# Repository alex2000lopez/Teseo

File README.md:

# Teseo
PCB for Teseo, a maze runner robot designed for MakersUPV

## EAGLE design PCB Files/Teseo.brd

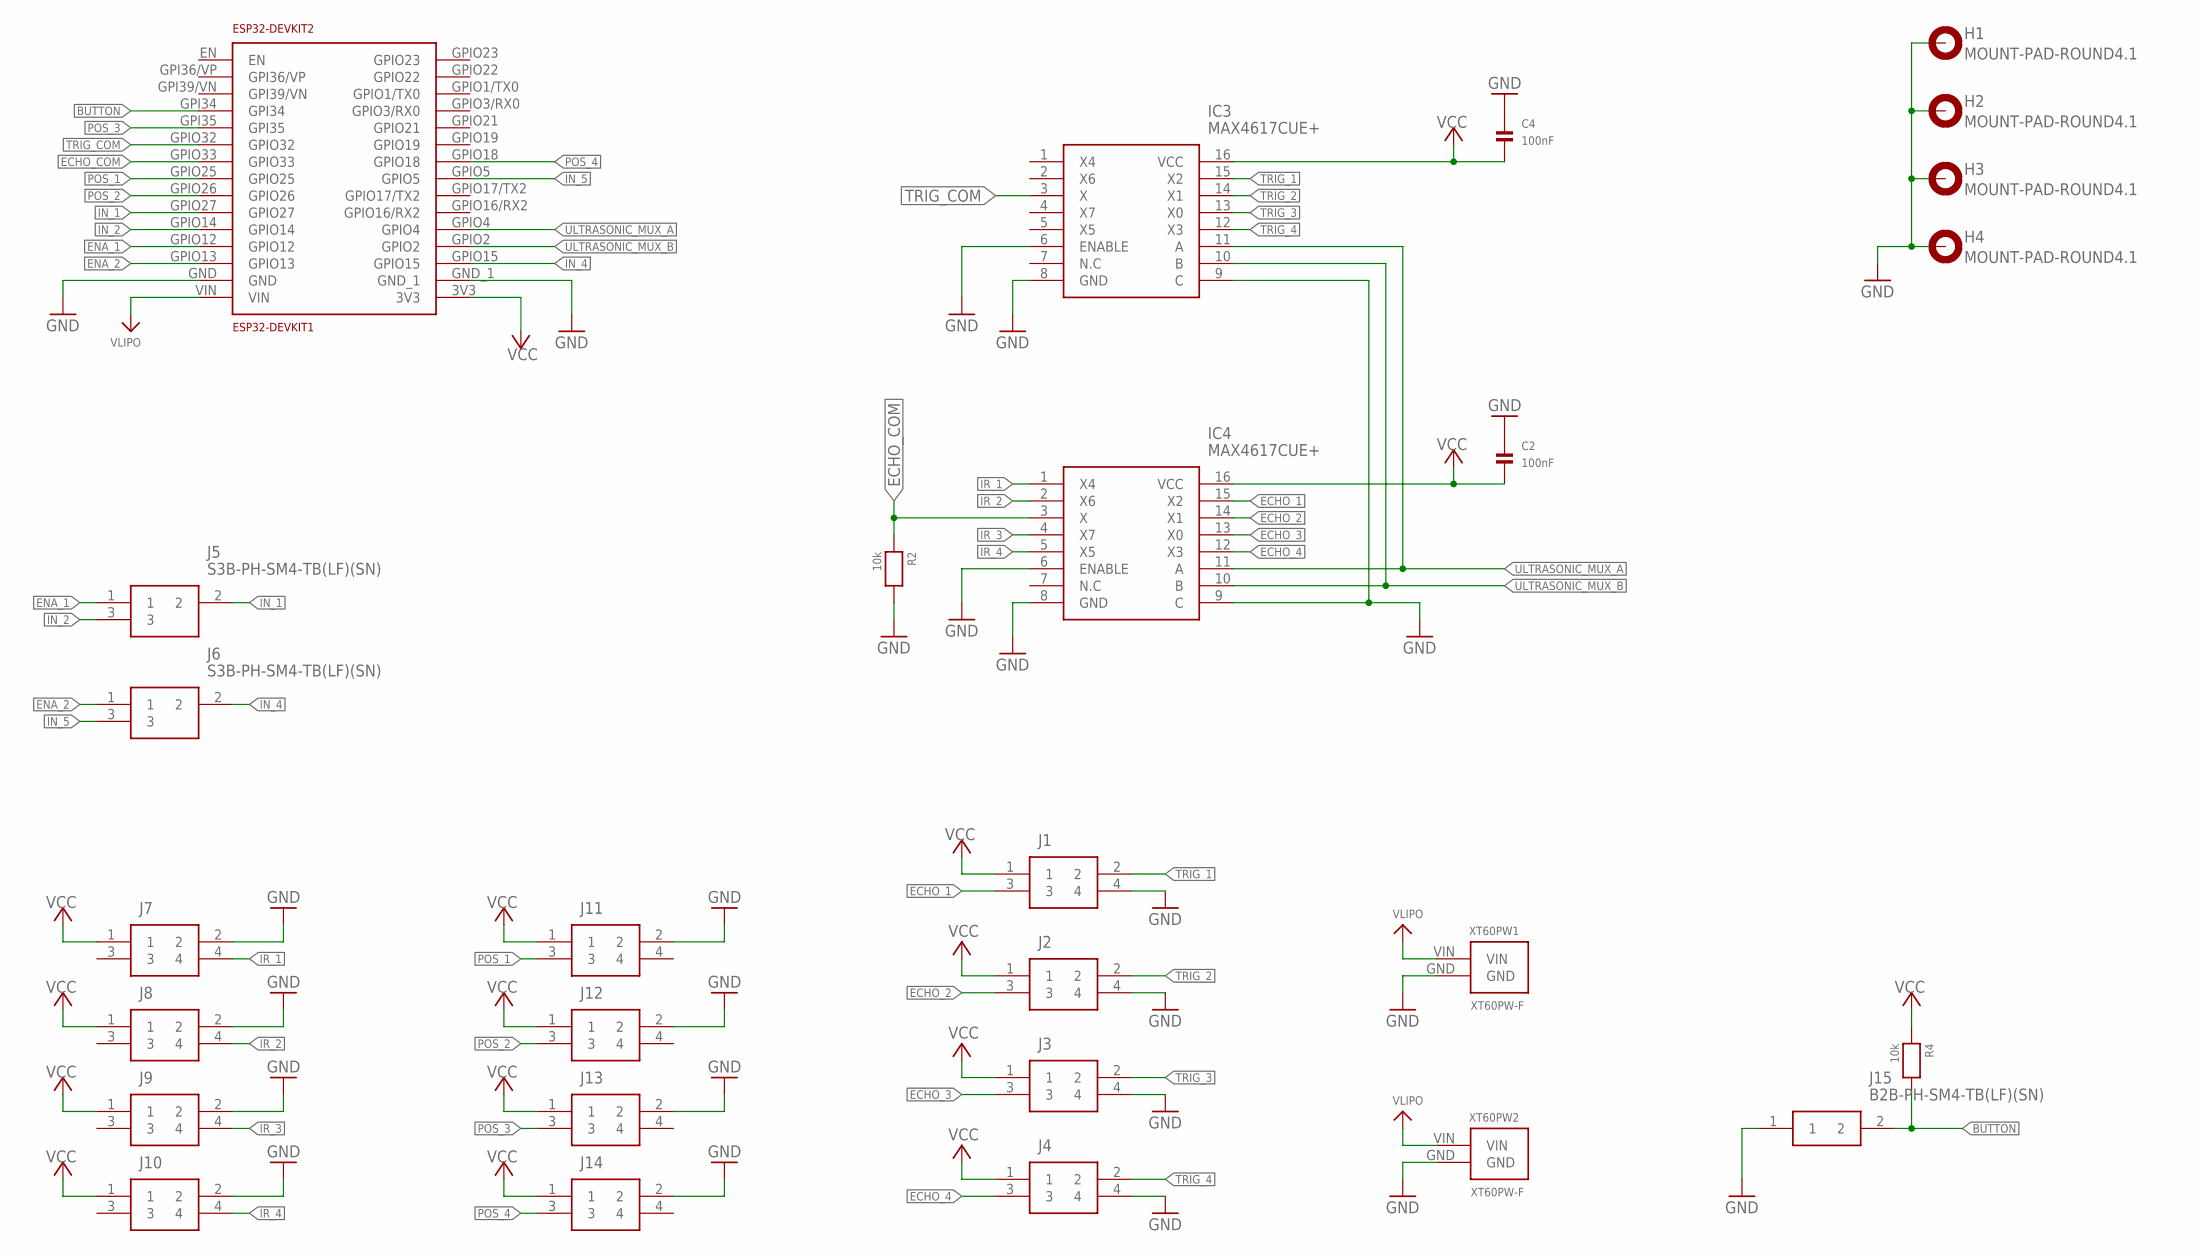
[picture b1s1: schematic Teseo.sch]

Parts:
C2, C4: 100nF; 0805
ESP32-DEVKIT2: ESP32-DEVKIT1
H1, H2, H3, H4: MOUNT-PAD-ROUND4.1; 4,1-PAD
IC3, IC4: MAX4617CUE+; SOP65P640X110-16N
J1, J2, J3, J4, J7, J8, J9, J10, J11, J12, J13, J14: S4B-PH-SM4-TB(LF)(SN); S4B-PH-SM4-TB
J5, J6: S3B-PH-SM4-TB(LF)(SN); S3B-PH-SM4-TB
J15: B2B-PH-SM4-TB(LF)(SN); B2B-PH-SM4-TB
R2, R4: 10k; _0805
XT60PW1, XT60PW2: XT60PW-F

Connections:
BUTTON: ESP32-DEVKIT2.GPI34, J15.2, R4.2
ECHO_1: IC4.15 (X2), J1.3
ECHO_2: IC4.14 (X1), J2.3
ECHO_3: IC4.13 (X0), J3.3
ECHO_4: IC4.12 (X3), J4.3
ECHO_COM: ESP32-DEVKIT2.GPIO33, IC4.3 (X), R2.1
ENA_1: ESP32-DEVKIT2.GPIO12, J5.1
ENA_2: ESP32-DEVKIT2.GPIO13, J6.1
GND: C2.1, C4.1, ESP32-DEVKIT2.GND, ESP32-DEVKIT2.GND_1, H1.B4,1, H2.B4,1, H3.B4,1, H4.B4,1, IC3.6 (ENABLE), IC3.8 (GND), IC3.9 (C), IC4.6 (ENABLE), IC4.8 (GND), IC4.9 (C), J1.4, J2.4, J3.4, J4.4, J7.2, J8.2, J9.2, J10.2, J11.2, J12.2, J13.2, J14.2, J15.1, R2.2, XT60PW1.GND, XT60PW2.GND
IN_1: ESP32-DEVKIT2.GPIO27, J5.2
IN_2: ESP32-DEVKIT2.GPIO14, J5.3
IN_4: ESP32-DEVKIT2.GPIO15, J6.2
IN_5: ESP32-DEVKIT2.GPIO5, J6.3
IR_1: IC4.1 (X4), J7.4
IR_2: IC4.2 (X6), J8.4
IR_3: IC4.4 (X7), J9.4
IR_4: IC4.5 (X5), J10.4
POS_1: ESP32-DEVKIT2.GPIO25, J11.3
POS_2: ESP32-DEVKIT2.GPIO26, J12.3
POS_3: ESP32-DEVKIT2.GPI35, J13.3
POS_4: ESP32-DEVKIT2.GPIO18, J14.3
TRIG_1: IC3.15 (X2), J1.2
TRIG_2: IC3.14 (X1), J2.2
TRIG_3: IC3.13 (X0), J3.2
TRIG_4: IC3.12 (X3), J4.2
TRIG_COM: ESP32-DEVKIT2.GPIO32, IC3.3 (X)
ULTRASONIC_MUX_A: ESP32-DEVKIT2.GPIO4, IC3.11 (A), IC4.11 (A)
ULTRASONIC_MUX_B: ESP32-DEVKIT2.GPIO2, IC3.10 (B), IC4.10 (B)
VCC: C2.2, C4.2, ESP32-DEVKIT2.3V3, IC3.16 (VCC), IC4.16 (VCC), J1.1, J2.1, J3.1, J4.1, J7.1, J8.1, J9.1, J10.1, J11.1, J12.1, J13.1, J14.1, R4.1
VLIPO: ESP32-DEVKIT2.VIN, XT60PW1.VIN, XT60PW2.VIN

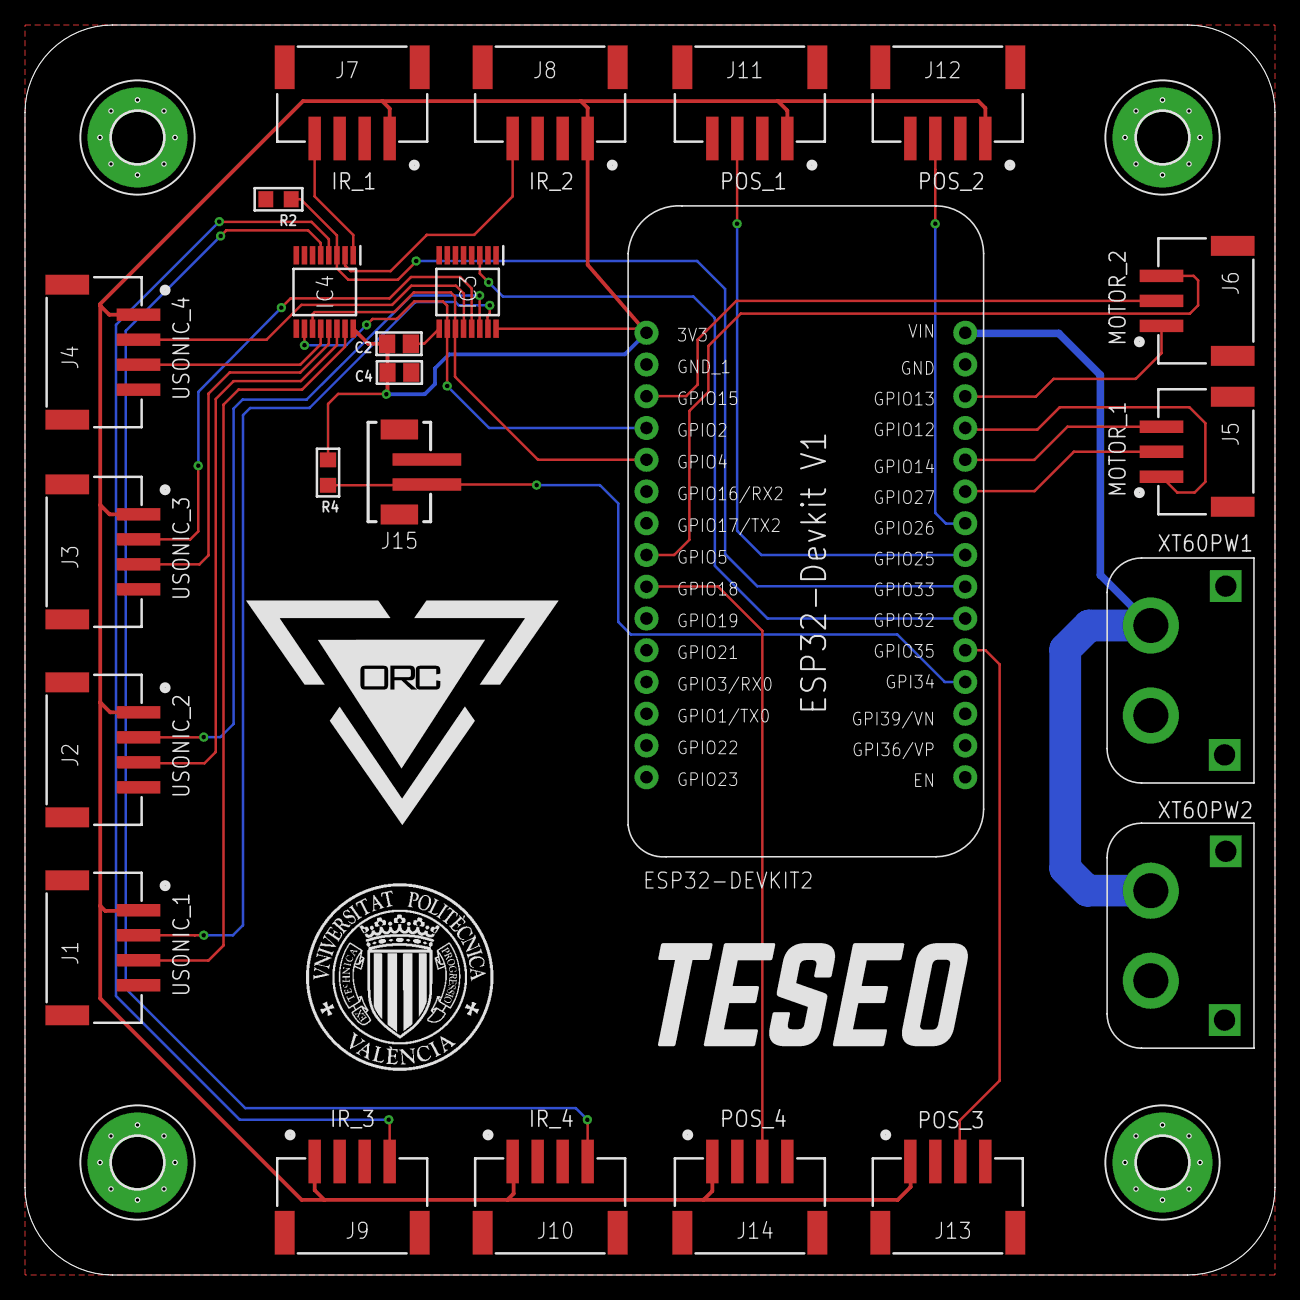
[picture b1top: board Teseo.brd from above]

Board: 2 copper layers, 100.0 x 100.0 mm, 29 parts (1 on the bottom side), 30 nets.

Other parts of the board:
U$1: OSHW-LOGO-L

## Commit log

2020-09-21 Files added

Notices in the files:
parts and their libraries:
microbuilder: This work is placed in the public domain, and may be freely used for commercial and non-commercial work with the following conditions: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
SparkFun-Aesthetics: Licensing: Creative Commons ShareAlike 4.0 International - https://creativecommons.org/licenses/by-sa/4.0
